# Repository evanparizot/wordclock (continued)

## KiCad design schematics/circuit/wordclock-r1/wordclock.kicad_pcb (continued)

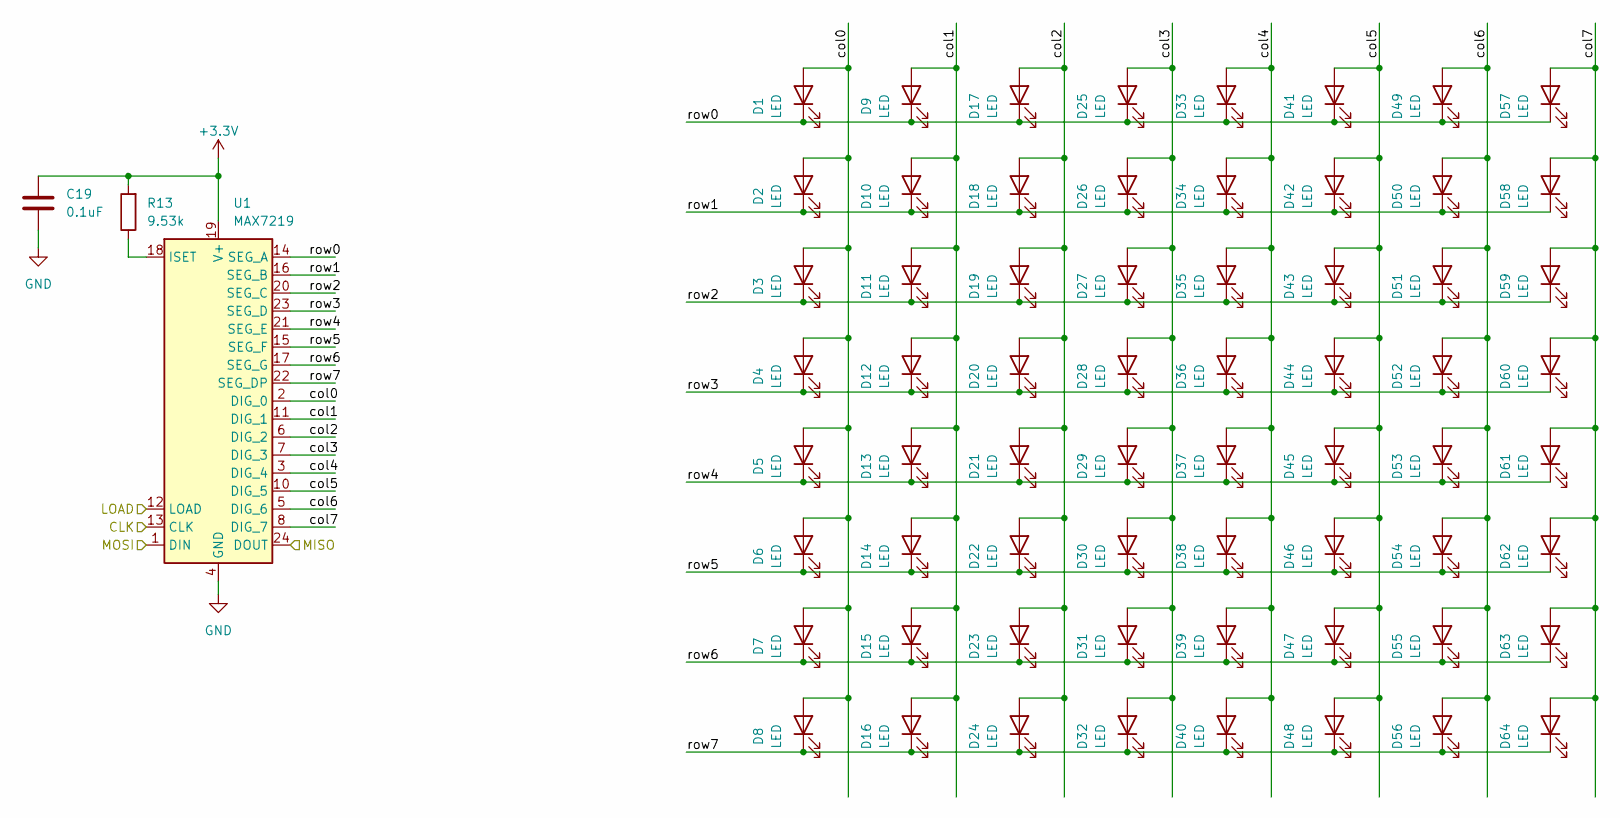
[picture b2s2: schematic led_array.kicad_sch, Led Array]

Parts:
C19: 0.1uF; C_0805_2012Metric
D1, D2, D3, D4, D5, D6, D7, D8, D9, D10, D11, D12, D13, D14, D15, D16, D17, D18, D19, D20, D21, D22, D23, D24, D25, D26, D27, D28, D29, D30, D31, D32, D33, D34, D35, D36, D37, D38, D39, D40, D41, D42, D43, D44, D45, D46, D47, D48, D49, D50, D51, D52, D53, D54, D55, D56, D57, D58, D59, D60, D61, D62, D63, D64: LED; LED_2010_5025Metric_Pad1.52x2.65mm_HandSolder
R13: 9.53k; R_0805_2012Metric
U1: MAX7219; SOIC-24W_7.5x15.4mm_P1.27mm

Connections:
+3.3V: C19.1, R13.2, U1.19 (V+); also elsewhere on the board
/Led Array 1/MISO: U1.24 (DOUT); also elsewhere on the board
/Led Array 1/col0: D1.2 (A), D2.2 (A), D3.2 (A), D4.2 (A), D5.2 (A), D6.2 (A), D7.2 (A), D8.2 (A), U1.2 (DIG_0)
/Led Array 1/col1: D9.2 (A), D10.2 (A), D11.2 (A), D12.2 (A), D13.2 (A), D14.2 (A), D15.2 (A), D16.2 (A), U1.11 (DIG_1)
/Led Array 1/col2: D17.2 (A), D18.2 (A), D19.2 (A), D20.2 (A), D21.2 (A), D22.2 (A), D23.2 (A), D24.2 (A), U1.6 (DIG_2)
/Led Array 1/col3: D25.2 (A), D26.2 (A), D27.2 (A), D28.2 (A), D29.2 (A), D30.2 (A), D31.2 (A), D32.2 (A), U1.7 (DIG_3)
/Led Array 1/col4: D33.2 (A), D34.2 (A), D35.2 (A), D36.2 (A), D37.2 (A), D38.2 (A), D39.2 (A), D40.2 (A), U1.3 (DIG_4)
/Led Array 1/col5: D41.2 (A), D42.2 (A), D43.2 (A), D44.2 (A), D45.2 (A), D46.2 (A), D47.2 (A), D48.2 (A), U1.10 (DIG_5)
/Led Array 1/col6: D49.2 (A), D50.2 (A), D51.2 (A), D52.2 (A), D53.2 (A), D54.2 (A), D55.2 (A), D56.2 (A), U1.5 (DIG_6)
/Led Array 1/col7: D57.2 (A), D58.2 (A), D59.2 (A), D60.2 (A), D61.2 (A), D62.2 (A), D63.2 (A), D64.2 (A), U1.8 (DIG_7)
/Led Array 1/row0: D1.1 (K), D9.1 (K), D17.1 (K), D25.1 (K), D33.1 (K), D41.1 (K), D49.1 (K), D57.1 (K), U1.14 (SEG_A)
/Led Array 1/row1: D2.1 (K), D10.1 (K), D18.1 (K), D26.1 (K), D34.1 (K), D42.1 (K), D50.1 (K), D58.1 (K), U1.16 (SEG_B)
/Led Array 1/row2: D3.1 (K), D11.1 (K), D19.1 (K), D27.1 (K), D35.1 (K), D43.1 (K), D51.1 (K), D59.1 (K), U1.20 (SEG_C)
/Led Array 1/row3: D4.1 (K), D12.1 (K), D20.1 (K), D28.1 (K), D36.1 (K), D44.1 (K), D52.1 (K), D60.1 (K), U1.23 (SEG_D)
/Led Array 1/row4: D5.1 (K), D13.1 (K), D21.1 (K), D29.1 (K), D37.1 (K), D45.1 (K), D53.1 (K), D61.1 (K), U1.21 (SEG_E)
/Led Array 1/row5: D6.1 (K), D14.1 (K), D22.1 (K), D30.1 (K), D38.1 (K), D46.1 (K), D54.1 (K), D62.1 (K), U1.15 (SEG_F)
/Led Array 1/row6: D7.1 (K), D15.1 (K), D23.1 (K), D31.1 (K), D39.1 (K), D47.1 (K), D55.1 (K), D63.1 (K), U1.17 (SEG_G)
/Led Array 1/row7: D8.1 (K), D16.1 (K), D24.1 (K), D32.1 (K), D40.1 (K), D48.1 (K), D56.1 (K), D64.1 (K), U1.22 (SEG_DP)
GND: C19.2, U1.4 (GND), U1.9 (GND); also elsewhere on the board
unnamed: R13.1, U1.18 (ISET)
SPI2_CLK: U1.13 (CLK); also elsewhere on the board
SPI2_LOAD: U1.12 (LOAD); also elsewhere on the board
SPI2_MOSI: U1.1 (DIN); also elsewhere on the board

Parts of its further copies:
C20, C21, C22: 0.1uF; C_0805_2012Metric
D65, D66, D67, D68, D69, D70, D71, D72, D73, D74, D75, D76, D77, D78, D79, D80, D81, D82, D83, D84, D85, D86, D87, D88, D89, D90, D91, D92, D93, D94, D95, D96, D97, D98, D99, D100, D101, D102, D103, D104, D105, D106, D107, D108, D109, D110, D111, D112, D113, D114, D115, D116, D117, D118, D119, D120, D121, D122, D123, D124, D125, D126, D127, D128, D129, D130, D131, D132, D133, D134, D135, D136, D137, D138, D139, D140, D141, D142, D143, D144, D145, D146, D147, D148, D149, D150, D151, D152, D153, D154, D155, D156, D157, D158, D159, D160, D161, D162, D163, D164, D165, D166, D167, D168, D169, D170, D171, D172, D173, D174, D175, D176, D177, D178, D179, D180, D181, D182, D183, D184, D185, D186, D187, D188, D189, D190, D191, D192, D193, D194, D195, D196, D197, D198, D199, D200, D201, D202, D203, D204, D205, D206, D207, D208, D209, D210, D211, D212, D213, D214, D215, D216, D217, D218, D219, D220, D221, D222, D223, D224, D225, D226, D227, D228, D229, D230, D231, D232, D233, D234, D235, D236, D237, D238, D239, D240, D241, D242, D243, D244, D245, D246, D247, D248, D249, D250, D251, D252, D253, D254, D255, D256: LED; LED_2010_5025Metric_Pad1.52x2.65mm_HandSolder
R14, R15, R16: 9.53k; R_0805_2012Metric
U2, U3, U4: MAX7219; SOIC-24W_7.5x15.4mm_P1.27mm

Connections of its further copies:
+3.3V: C20.1, C21.1, C22.1, R14.2, R15.2, R16.2, U2.19 (V+), U3.19 (V+), U4.19 (V+); also elsewhere on the board
/Led Array 1/MISO: U2.1 (DIN); also elsewhere on the board
/Led Array 2/MISO: U2.24 (DOUT), U3.1 (DIN)
/Led Array 2/col0: D65.2 (A), D66.2 (A), D67.2 (A), D68.2 (A), D69.2 (A), D70.2 (A), D71.2 (A), D72.2 (A), U2.2 (DIG_0)
/Led Array 2/col1: D73.2 (A), D74.2 (A), D75.2 (A), D76.2 (A), D77.2 (A), D78.2 (A), D79.2 (A), D80.2 (A), U2.11 (DIG_1)
/Led Array 2/col2: D81.2 (A), D82.2 (A), D83.2 (A), D84.2 (A), D85.2 (A), D86.2 (A), D87.2 (A), D88.2 (A), U2.6 (DIG_2)
/Led Array 2/col3: D89.2 (A), D90.2 (A), D91.2 (A), D92.2 (A), D93.2 (A), D94.2 (A), D95.2 (A), D96.2 (A), U2.7 (DIG_3)
/Led Array 2/col4: D97.2 (A), D98.2 (A), D99.2 (A), D100.2 (A), D101.2 (A), D102.2 (A), D103.2 (A), D104.2 (A), U2.3 (DIG_4)
/Led Array 2/col5: D105.2 (A), D106.2 (A), D107.2 (A), D108.2 (A), D109.2 (A), D110.2 (A), D111.2 (A), D112.2 (A), U2.10 (DIG_5)
/Led Array 2/col6: D113.2 (A), D114.2 (A), D115.2 (A), D116.2 (A), D117.2 (A), D118.2 (A), D119.2 (A), D120.2 (A), U2.5 (DIG_6)
/Led Array 2/col7: D121.2 (A), D122.2 (A), D123.2 (A), D124.2 (A), D125.2 (A), D126.2 (A), D127.2 (A), D128.2 (A), U2.8 (DIG_7)
/Led Array 2/row0: D65.1 (K), D73.1 (K), D81.1 (K), D89.1 (K), D97.1 (K), D105.1 (K), D113.1 (K), D121.1 (K), U2.14 (SEG_A)
/Led Array 2/row1: D66.1 (K), D74.1 (K), D82.1 (K), D90.1 (K), D98.1 (K), D106.1 (K), D114.1 (K), D122.1 (K), U2.16 (SEG_B)
/Led Array 2/row2: D67.1 (K), D75.1 (K), D83.1 (K), D91.1 (K), D99.1 (K), D107.1 (K), D115.1 (K), D123.1 (K), U2.20 (SEG_C)
/Led Array 2/row3: D68.1 (K), D76.1 (K), D84.1 (K), D92.1 (K), D100.1 (K), D108.1 (K), D116.1 (K), D124.1 (K), U2.23 (SEG_D)
/Led Array 2/row4: D69.1 (K), D77.1 (K), D85.1 (K), D93.1 (K), D101.1 (K), D109.1 (K), D117.1 (K), D125.1 (K), U2.21 (SEG_E)
/Led Array 2/row5: D70.1 (K), D78.1 (K), D86.1 (K), D94.1 (K), D102.1 (K), D110.1 (K), D118.1 (K), D126.1 (K), U2.15 (SEG_F)
/Led Array 2/row6: D71.1 (K), D79.1 (K), D87.1 (K), D95.1 (K), D103.1 (K), D111.1 (K), D119.1 (K), D127.1 (K), U2.17 (SEG_G)
/Led Array 2/row7: D72.1 (K), D80.1 (K), D88.1 (K), D96.1 (K), D104.1 (K), D112.1 (K), D120.1 (K), D128.1 (K), U2.22 (SEG_DP)
/Led Array 3/MISO: U3.24 (DOUT), U4.1 (DIN)
/Led Array 3/col0: D129.2 (A), D130.2 (A), D131.2 (A), D132.2 (A), D133.2 (A), D134.2 (A), D135.2 (A), D136.2 (A), U3.2 (DIG_0)
/Led Array 3/col1: D137.2 (A), D138.2 (A), D139.2 (A), D140.2 (A), D141.2 (A), D142.2 (A), D143.2 (A), D144.2 (A), U3.11 (DIG_1)
/Led Array 3/col2: D145.2 (A), D146.2 (A), D147.2 (A), D148.2 (A), D149.2 (A), D150.2 (A), D151.2 (A), D152.2 (A), U3.6 (DIG_2)
/Led Array 3/col3: D153.2 (A), D154.2 (A), D155.2 (A), D156.2 (A), D157.2 (A), D158.2 (A), D159.2 (A), D160.2 (A), U3.7 (DIG_3)
/Led Array 3/col4: D161.2 (A), D162.2 (A), D163.2 (A), D164.2 (A), D165.2 (A), D166.2 (A), D167.2 (A), D168.2 (A), U3.3 (DIG_4)
/Led Array 3/col5: D169.2 (A), D170.2 (A), D171.2 (A), D172.2 (A), D173.2 (A), D174.2 (A), D175.2 (A), D176.2 (A), U3.10 (DIG_5)
/Led Array 3/col6: D177.2 (A), D178.2 (A), D179.2 (A), D180.2 (A), D181.2 (A), D182.2 (A), D183.2 (A), D184.2 (A), U3.5 (DIG_6)
/Led Array 3/col7: D185.2 (A), D186.2 (A), D187.2 (A), D188.2 (A), D189.2 (A), D190.2 (A), D191.2 (A), D192.2 (A), U3.8 (DIG_7)
/Led Array 3/row0: D129.1 (K), D137.1 (K), D145.1 (K), D153.1 (K), D161.1 (K), D169.1 (K), D177.1 (K), D185.1 (K), U3.14 (SEG_A)
/Led Array 3/row1: D130.1 (K), D138.1 (K), D146.1 (K), D154.1 (K), D162.1 (K), D170.1 (K), D178.1 (K), D186.1 (K), U3.16 (SEG_B)
/Led Array 3/row2: D131.1 (K), D139.1 (K), D147.1 (K), D155.1 (K), D163.1 (K), D171.1 (K), D179.1 (K), D187.1 (K), U3.20 (SEG_C)
/Led Array 3/row3: D132.1 (K), D140.1 (K), D148.1 (K), D156.1 (K), D164.1 (K), D172.1 (K), D180.1 (K), D188.1 (K), U3.23 (SEG_D)
/Led Array 3/row4: D133.1 (K), D141.1 (K), D149.1 (K), D157.1 (K), D165.1 (K), D173.1 (K), D181.1 (K), D189.1 (K), U3.21 (SEG_E)
/Led Array 3/row5: D134.1 (K), D142.1 (K), D150.1 (K), D158.1 (K), D166.1 (K), D174.1 (K), D182.1 (K), D190.1 (K), U3.15 (SEG_F)
/Led Array 3/row6: D135.1 (K), D143.1 (K), D151.1 (K), D159.1 (K), D167.1 (K), D175.1 (K), D183.1 (K), D191.1 (K), U3.17 (SEG_G)
/Led Array 3/row7: D136.1 (K), D144.1 (K), D152.1 (K), D160.1 (K), D168.1 (K), D176.1 (K), D184.1 (K), D192.1 (K), U3.22 (SEG_DP)
/Led Array 4/col0: D193.2 (A), D194.2 (A), D195.2 (A), D196.2 (A), D197.2 (A), D198.2 (A), D199.2 (A), D200.2 (A), U4.2 (DIG_0)
/Led Array 4/col1: D201.2 (A), D202.2 (A), D203.2 (A), D204.2 (A), D205.2 (A), D206.2 (A), D207.2 (A), D208.2 (A), U4.11 (DIG_1)
/Led Array 4/col2: D209.2 (A), D210.2 (A), D211.2 (A), D212.2 (A), D213.2 (A), D214.2 (A), D215.2 (A), D216.2 (A), U4.6 (DIG_2)
/Led Array 4/col3: D217.2 (A), D218.2 (A), D219.2 (A), D220.2 (A), D221.2 (A), D222.2 (A), D223.2 (A), D224.2 (A), U4.7 (DIG_3)
/Led Array 4/col4: D225.2 (A), D226.2 (A), D227.2 (A), D228.2 (A), D229.2 (A), D230.2 (A), D231.2 (A), D232.2 (A), U4.3 (DIG_4)
/Led Array 4/col5: D233.2 (A), D234.2 (A), D235.2 (A), D236.2 (A), D237.2 (A), D238.2 (A), D239.2 (A), D240.2 (A), U4.10 (DIG_5)
/Led Array 4/col6: D241.2 (A), D242.2 (A), D243.2 (A), D244.2 (A), D245.2 (A), D246.2 (A), D247.2 (A), D248.2 (A), U4.5 (DIG_6)
/Led Array 4/col7: D249.2 (A), D250.2 (A), D251.2 (A), D252.2 (A), D253.2 (A), D254.2 (A), D255.2 (A), D256.2 (A), U4.8 (DIG_7)
/Led Array 4/row0: D193.1 (K), D201.1 (K), D209.1 (K), D217.1 (K), D225.1 (K), D233.1 (K), D241.1 (K), D249.1 (K), U4.14 (SEG_A)
/Led Array 4/row1: D194.1 (K), D202.1 (K), D210.1 (K), D218.1 (K), D226.1 (K), D234.1 (K), D242.1 (K), D250.1 (K), U4.16 (SEG_B)
/Led Array 4/row2: D195.1 (K), D203.1 (K), D211.1 (K), D219.1 (K), D227.1 (K), D235.1 (K), D243.1 (K), D251.1 (K), U4.20 (SEG_C)
/Led Array 4/row3: D196.1 (K), D204.1 (K), D212.1 (K), D220.1 (K), D228.1 (K), D236.1 (K), D244.1 (K), D252.1 (K), U4.23 (SEG_D)
/Led Array 4/row4: D197.1 (K), D205.1 (K), D213.1 (K), D221.1 (K), D229.1 (K), D237.1 (K), D245.1 (K), D253.1 (K), U4.21 (SEG_E)
/Led Array 4/row5: D198.1 (K), D206.1 (K), D214.1 (K), D222.1 (K), D230.1 (K), D238.1 (K), D246.1 (K), D254.1 (K), U4.15 (SEG_F)
/Led Array 4/row6: D199.1 (K), D207.1 (K), D215.1 (K), D223.1 (K), D231.1 (K), D239.1 (K), D247.1 (K), D255.1 (K), U4.17 (SEG_G)
/Led Array 4/row7: D200.1 (K), D208.1 (K), D216.1 (K), D224.1 (K), D232.1 (K), D240.1 (K), D248.1 (K), D256.1 (K), U4.22 (SEG_DP)
GND: C20.2, C21.2, C22.2, U2.4 (GND), U2.9 (GND), U3.4 (GND), U3.9 (GND), U4.4 (GND), U4.9 (GND); also elsewhere on the board
unnamed: R14.1, U2.18 (ISET)
unnamed: R15.1, U3.18 (ISET)
unnamed: R16.1, U4.18 (ISET)
SPI2_CLK: U2.13 (CLK), U3.13 (CLK), U4.13 (CLK); also elsewhere on the board
SPI2_LOAD: U2.12 (LOAD), U3.12 (LOAD), U4.12 (LOAD); also elsewhere on the board
SPI2_MISO: U4.24 (DOUT); also elsewhere on the board

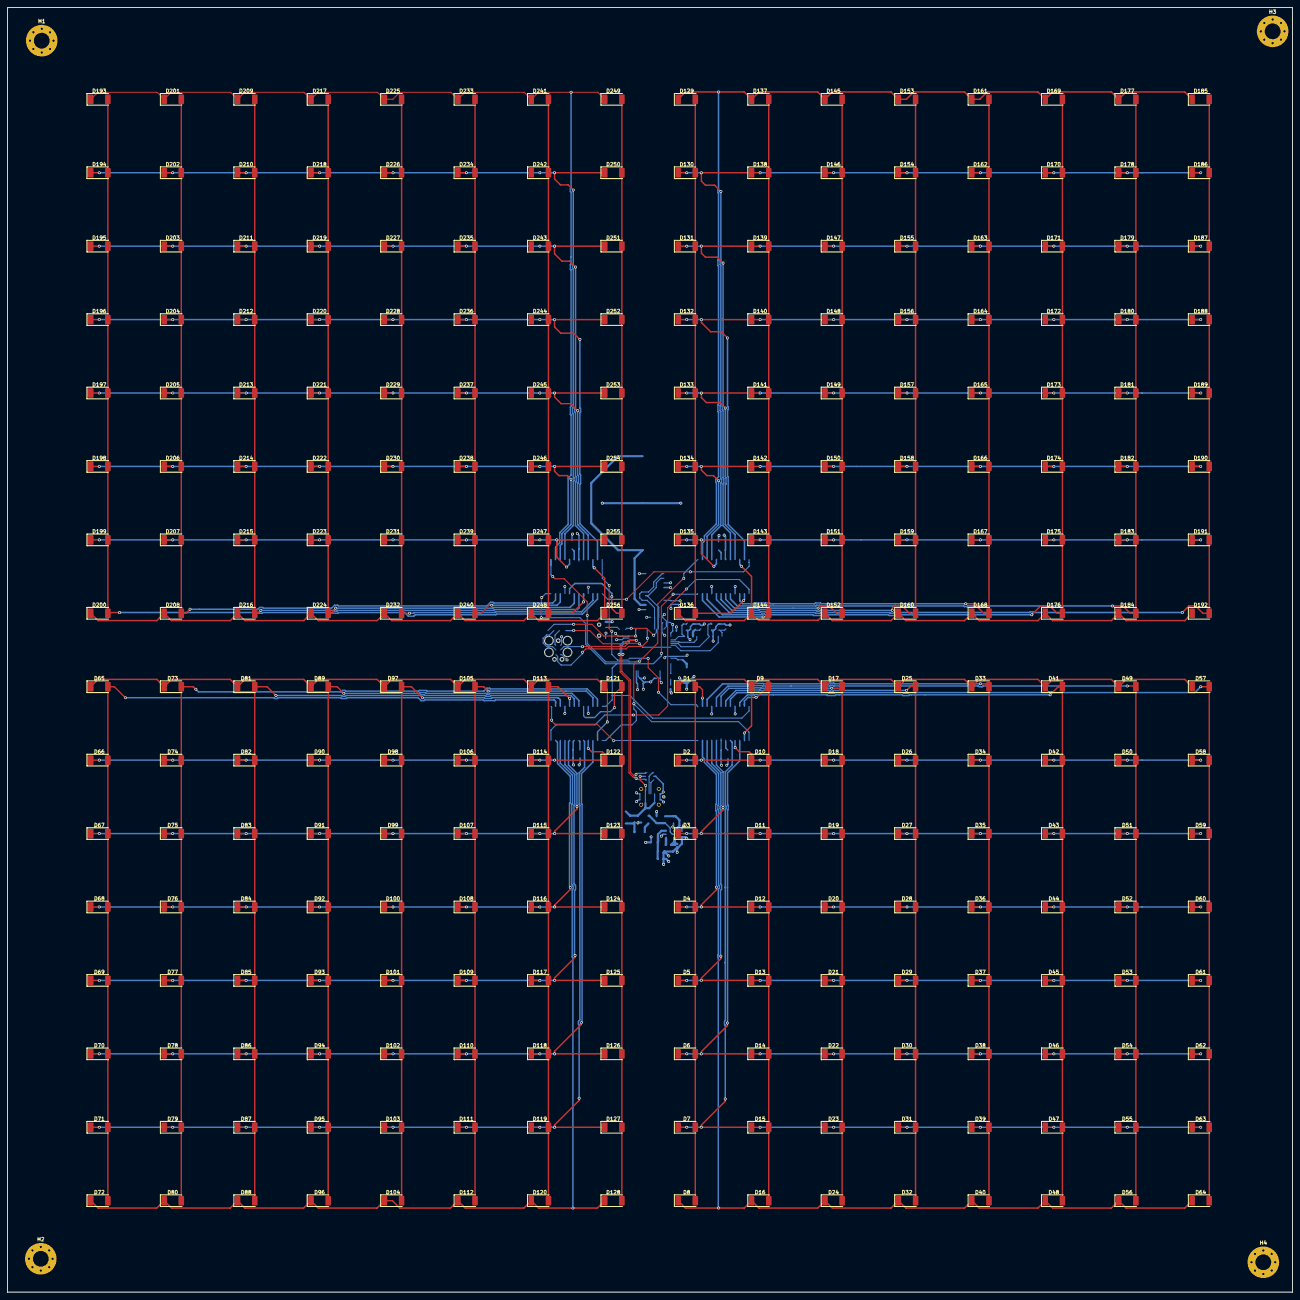
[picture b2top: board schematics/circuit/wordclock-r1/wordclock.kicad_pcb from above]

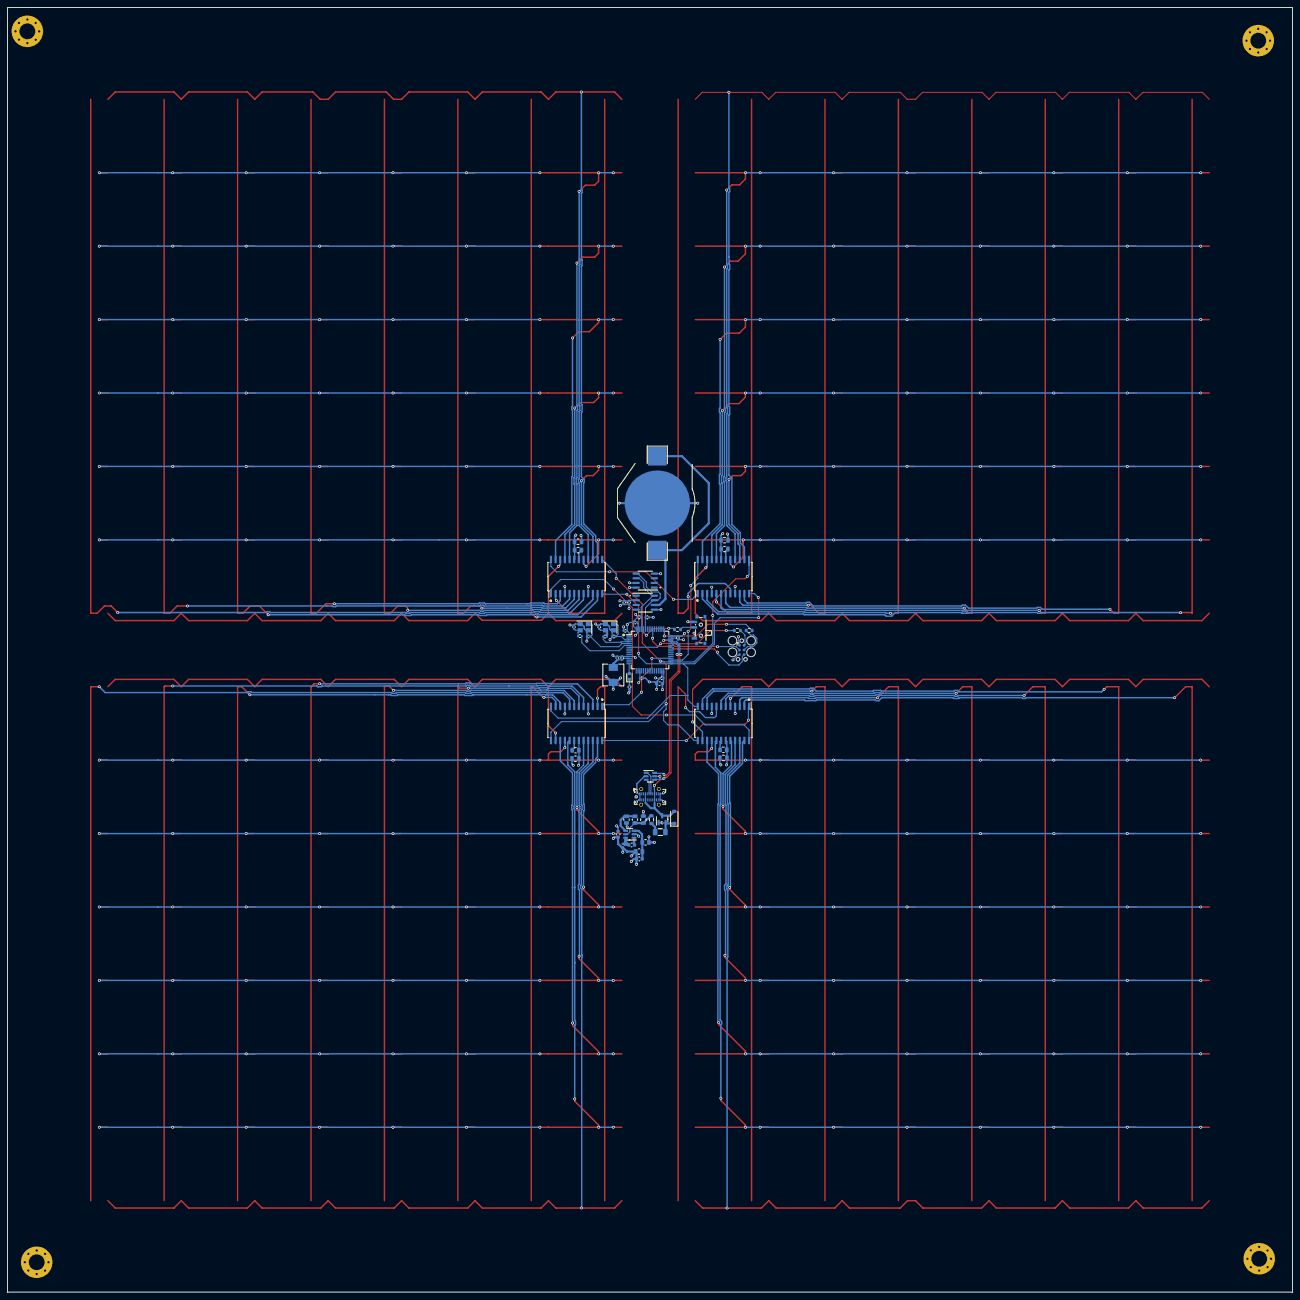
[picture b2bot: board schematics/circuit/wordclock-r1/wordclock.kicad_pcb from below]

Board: 4 copper layers, 350.0 x 349.9 mm, 320 parts (60 on the bottom side), 109 nets.

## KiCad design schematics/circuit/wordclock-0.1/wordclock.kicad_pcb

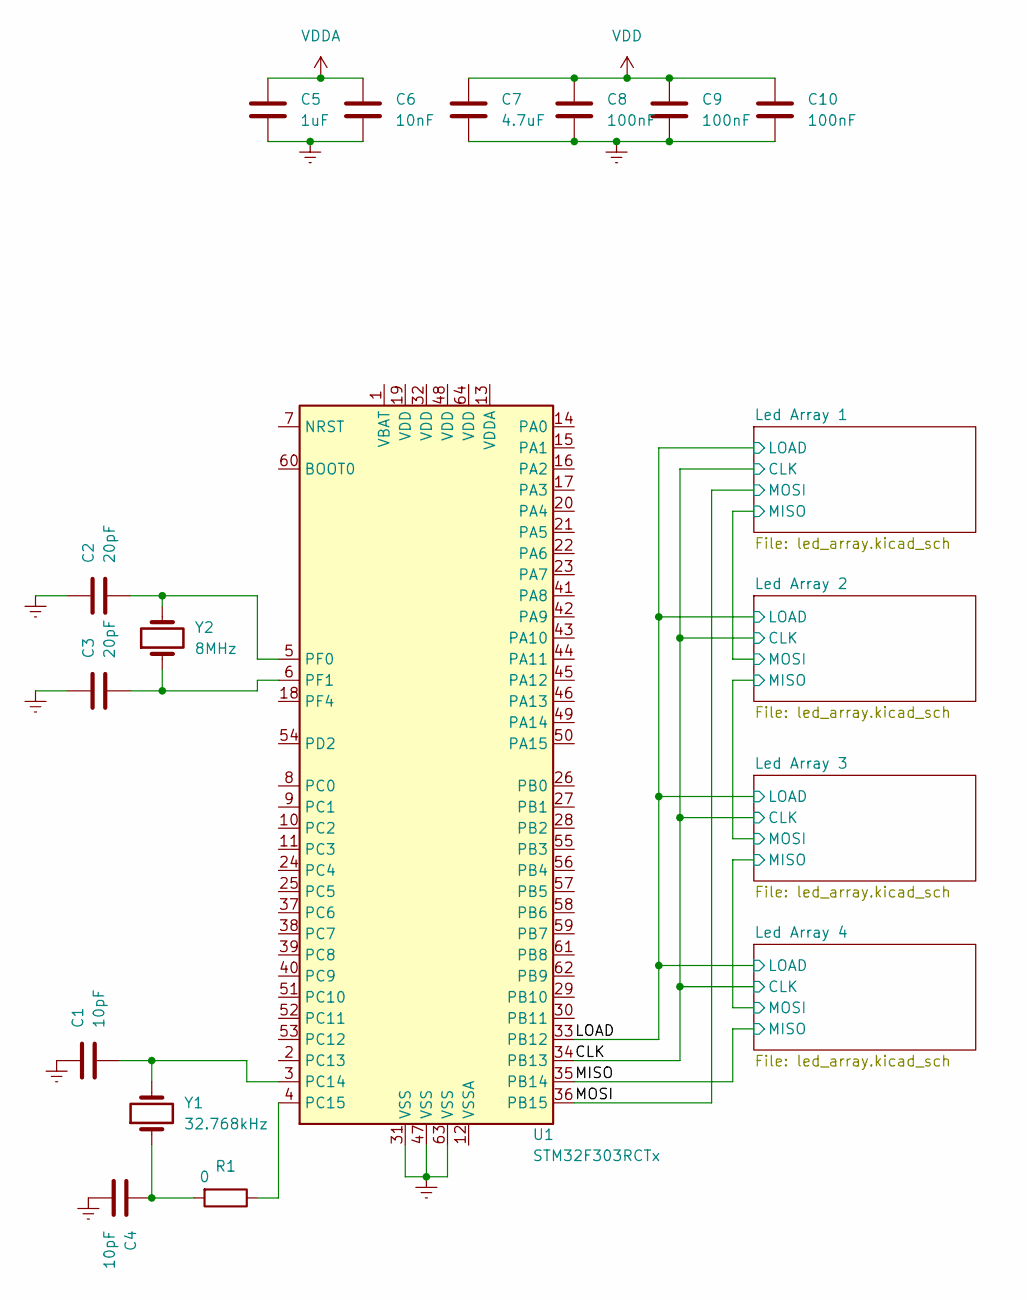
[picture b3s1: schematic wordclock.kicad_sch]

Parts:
C1, C4: 10pF; C_0805_2012Metric
C2, C3: 20pF; C_0805_2012Metric
C5: 1uF; C_0805_2012Metric
C6: 10nF; C_0805_2012Metric
C7: 4.7uF; C_0805_2012Metric
C8, C9, C10: 100nF; C_0805_2012Metric
R1: 0; R_1210_3225Metric
U1: STM32F303RCTx; LQFP-64_10x10mm_P0.5mm
Y1: 32.768kHz; Crystal_SMD_3225-4Pin_3.2x2.5mm
Y2: 8MHz; Crystal_SMD_3225-4Pin_3.2x2.5mm

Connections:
/CLK: U1.34 (PB13); also elsewhere on the board
/LOAD: U1.33 (PB12); also elsewhere on the board
/MISO: U1.35 (PB14); also elsewhere on the board
/MOSI: U1.36 (PB15); also elsewhere on the board
Earth: C1.1, C2.1, C3.1, C4.2, C5.2, C6.2, C7.2, C8.2, C9.2, C10.2, U1.31 (VSS), U1.47 (VSS), U1.63 (VSS)
unnamed: C4.1, R1.2, Y1.1
unnamed: C1.2, U1.3 (PC14), Y1.2
unnamed: R1.1, U1.4 (PC15)
unnamed: C2.2, U1.5 (PF0), Y2.2
unnamed: C3.2, U1.6 (PF1), Y2.1
VDD: C7.1, C8.1, C9.1, C10.1; also elsewhere on the board
VDDA: C5.1, C6.1

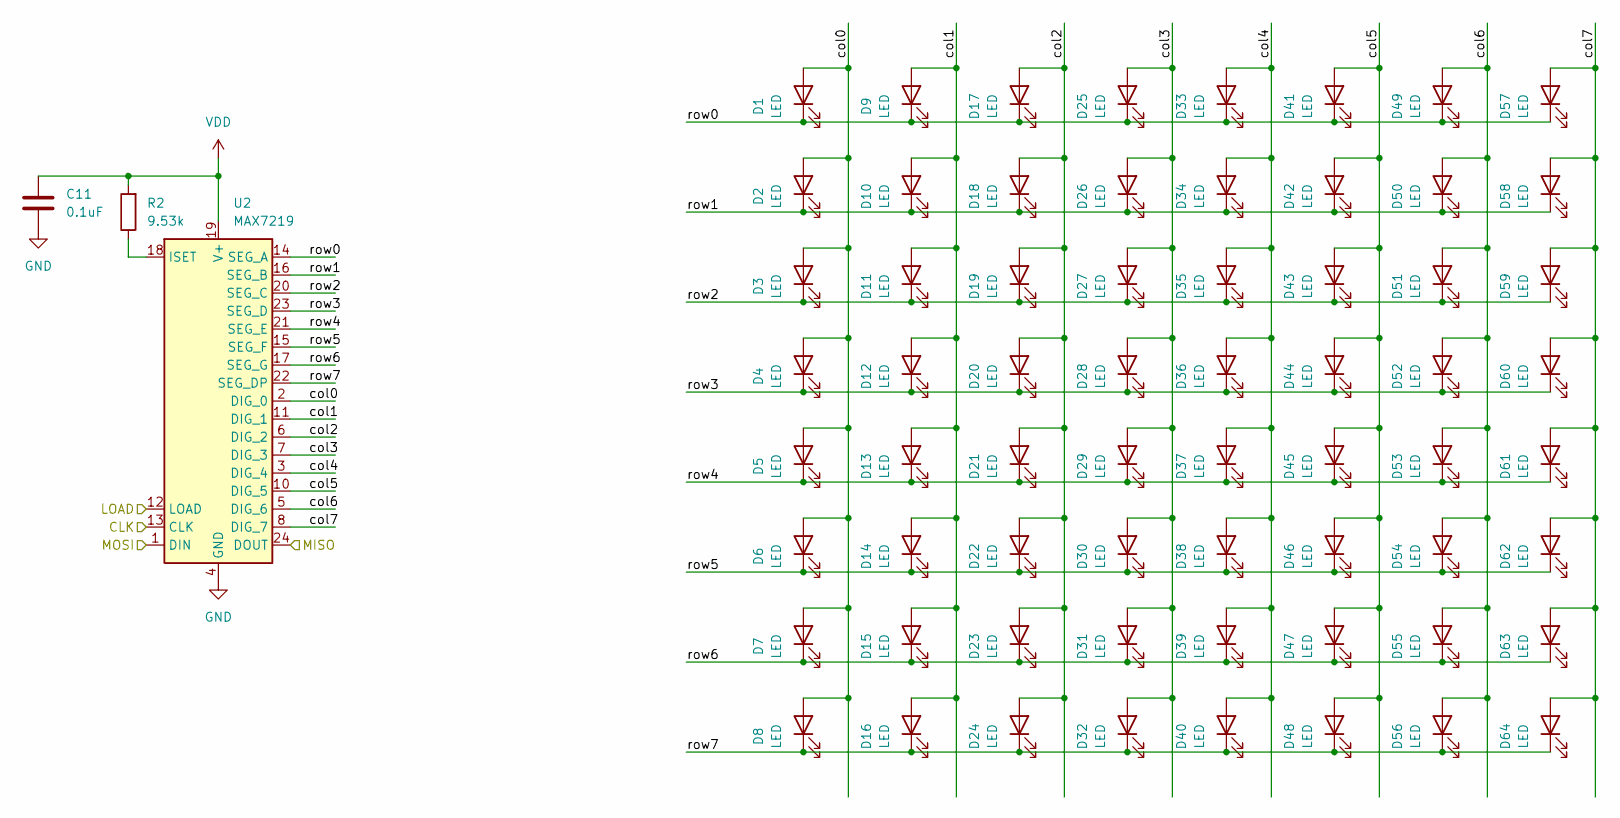
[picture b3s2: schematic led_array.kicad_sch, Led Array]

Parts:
C11: 0.1uF; C_0805_2012Metric
D1, D2, D3, D4, D5, D6, D7, D8, D9, D10, D11, D12, D13, D14, D15, D16, D17, D18, D19, D20, D21, D22, D23, D24, D25, D26, D27, D28, D29, D30, D31, D32, D33, D34, D35, D36, D37, D38, D39, D40, D41, D42, D43, D44, D45, D46, D47, D48, D49, D50, D51, D52, D53, D54, D55, D56, D57, D58, D59, D60, D61, D62, D63, D64: LED; LED_2010_5025Metric_Pad1.52x2.65mm_HandSolder
R2: 9.53k; R_0805_2012Metric
U2: MAX7219; SOIC-24W_7.5x15.4mm_P1.27mm

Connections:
/CLK: U2.13 (CLK); also elsewhere on the board
/LOAD: U2.12 (LOAD); also elsewhere on the board
/Led Array 1/MISO: U2.24 (DOUT); also elsewhere on the board
/Led Array 1/col0: D1.2 (A), D2.2 (A), D3.2 (A), D4.2 (A), D5.2 (A), D6.2 (A), D7.2 (A), D8.2 (A), U2.2 (DIG_0)
/Led Array 1/col1: D9.2 (A), D10.2 (A), D11.2 (A), D12.2 (A), D13.2 (A), D14.2 (A), D15.2 (A), D16.2 (A), U2.11 (DIG_1)
/Led Array 1/col2: D17.2 (A), D18.2 (A), D19.2 (A), D20.2 (A), D21.2 (A), D22.2 (A), D23.2 (A), D24.2 (A), U2.6 (DIG_2)
/Led Array 1/col3: D25.2 (A), D26.2 (A), D27.2 (A), D28.2 (A), D29.2 (A), D30.2 (A), D31.2 (A), D32.2 (A), U2.7 (DIG_3)
/Led Array 1/col4: D33.2 (A), D34.2 (A), D35.2 (A), D36.2 (A), D37.2 (A), D38.2 (A), D39.2 (A), D40.2 (A), U2.3 (DIG_4)
/Led Array 1/col5: D41.2 (A), D42.2 (A), D43.2 (A), D44.2 (A), D45.2 (A), D46.2 (A), D47.2 (A), D48.2 (A), U2.10 (DIG_5)
/Led Array 1/col6: D49.2 (A), D50.2 (A), D51.2 (A), D52.2 (A), D53.2 (A), D54.2 (A), D55.2 (A), D56.2 (A), U2.5 (DIG_6)
/Led Array 1/col7: D57.2 (A), D58.2 (A), D59.2 (A), D60.2 (A), D61.2 (A), D62.2 (A), D63.2 (A), D64.2 (A), U2.8 (DIG_7)
/Led Array 1/row0: D1.1 (K), D9.1 (K), D17.1 (K), D25.1 (K), D33.1 (K), D41.1 (K), D49.1 (K), D57.1 (K), U2.14 (SEG_A)
/Led Array 1/row1: D2.1 (K), D10.1 (K), D18.1 (K), D26.1 (K), D34.1 (K), D42.1 (K), D50.1 (K), D58.1 (K), U2.16 (SEG_B)
/Led Array 1/row2: D3.1 (K), D11.1 (K), D19.1 (K), D27.1 (K), D35.1 (K), D43.1 (K), D51.1 (K), D59.1 (K), U2.20 (SEG_C)
/Led Array 1/row3: D4.1 (K), D12.1 (K), D20.1 (K), D28.1 (K), D36.1 (K), D44.1 (K), D52.1 (K), D60.1 (K), U2.23 (SEG_D)
/Led Array 1/row4: D5.1 (K), D13.1 (K), D21.1 (K), D29.1 (K), D37.1 (K), D45.1 (K), D53.1 (K), D61.1 (K), U2.21 (SEG_E)
/Led Array 1/row5: D6.1 (K), D14.1 (K), D22.1 (K), D30.1 (K), D38.1 (K), D46.1 (K), D54.1 (K), D62.1 (K), U2.15 (SEG_F)
/Led Array 1/row6: D7.1 (K), D15.1 (K), D23.1 (K), D31.1 (K), D39.1 (K), D47.1 (K), D55.1 (K), D63.1 (K), U2.17 (SEG_G)
/Led Array 1/row7: D8.1 (K), D16.1 (K), D24.1 (K), D32.1 (K), D40.1 (K), D48.1 (K), D56.1 (K), D64.1 (K), U2.22 (SEG_DP)
/MOSI: U2.1 (DIN); also elsewhere on the board
GND: C11.2, U2.4 (GND), U2.9 (GND); also elsewhere on the board
unnamed: R2.1, U2.18 (ISET)
VDD: C11.1, R2.2, U2.19 (V+); also elsewhere on the board

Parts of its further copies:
C12, C13, C14: 0.1uF; C_0805_2012Metric
D65, D66, D67, D68, D69, D70, D71, D72, D73, D74, D75, D76, D77, D78, D79, D80, D81, D82, D83, D84, D85, D86, D87, D88, D89, D90, D91, D92, D93, D94, D95, D96, D97, D98, D99, D100, D101, D102, D103, D104, D105, D106, D107, D108, D109, D110, D111, D112, D113, D114, D115, D116, D117, D118, D119, D120, D121, D122, D123, D124, D125, D126, D127, D128, D129, D130, D131, D132, D133, D134, D135, D136, D137, D138, D139, D140, D141, D142, D143, D144, D145, D146, D147, D148, D149, D150, D151, D152, D153, D154, D155, D156, D157, D158, D159, D160, D161, D162, D163, D164, D165, D166, D167, D168, D169, D170, D171, D172, D173, D174, D175, D176, D177, D178, D179, D180, D181, D182, D183, D184, D185, D186, D187, D188, D189, D190, D191, D192, D193, D194, D195, D196, D197, D198, D199, D200, D201, D202, D203, D204, D205, D206, D207, D208, D209, D210, D211, D212, D213, D214, D215, D216, D217, D218, D219, D220, D221, D222, D223, D224, D225, D226, D227, D228, D229, D230, D231, D232, D233, D234, D235, D236, D237, D238, D239, D240, D241, D242, D243, D244, D245, D246, D247, D248, D249, D250, D251, D252, D253, D254, D255, D256: LED; LED_2010_5025Metric_Pad1.52x2.65mm_HandSolder
R3, R4, R5: 9.53k; R_0805_2012Metric
U3, U4, U5: MAX7219; SOIC-24W_7.5x15.4mm_P1.27mm

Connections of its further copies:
/CLK: U3.13 (CLK), U4.13 (CLK), U5.13 (CLK); also elsewhere on the board
/LOAD: U3.12 (LOAD), U4.12 (LOAD), U5.12 (LOAD); also elsewhere on the board
/Led Array 1/MISO: U3.1 (DIN); also elsewhere on the board
/Led Array 2/MISO: U3.24 (DOUT), U4.1 (DIN)
/Led Array 2/col0: D65.2 (A), D66.2 (A), D67.2 (A), D68.2 (A), D69.2 (A), D70.2 (A), D71.2 (A), D72.2 (A), U3.2 (DIG_0)
/Led Array 2/col1: D73.2 (A), D74.2 (A), D75.2 (A), D76.2 (A), D77.2 (A), D78.2 (A), D79.2 (A), D80.2 (A), U3.11 (DIG_1)
/Led Array 2/col2: D81.2 (A), D82.2 (A), D83.2 (A), D84.2 (A), D85.2 (A), D86.2 (A), D87.2 (A), D88.2 (A), U3.6 (DIG_2)
/Led Array 2/col3: D89.2 (A), D90.2 (A), D91.2 (A), D92.2 (A), D93.2 (A), D94.2 (A), D95.2 (A), D96.2 (A), U3.7 (DIG_3)
/Led Array 2/col4: D97.2 (A), D98.2 (A), D99.2 (A), D100.2 (A), D101.2 (A), D102.2 (A), D103.2 (A), D104.2 (A), U3.3 (DIG_4)
/Led Array 2/col5: D105.2 (A), D106.2 (A), D107.2 (A), D108.2 (A), D109.2 (A), D110.2 (A), D111.2 (A), D112.2 (A), U3.10 (DIG_5)
/Led Array 2/col6: D113.2 (A), D114.2 (A), D115.2 (A), D116.2 (A), D117.2 (A), D118.2 (A), D119.2 (A), D120.2 (A), U3.5 (DIG_6)
/Led Array 2/col7: D121.2 (A), D122.2 (A), D123.2 (A), D124.2 (A), D125.2 (A), D126.2 (A), D127.2 (A), D128.2 (A), U3.8 (DIG_7)
/Led Array 2/row0: D65.1 (K), D73.1 (K), D81.1 (K), D89.1 (K), D97.1 (K), D105.1 (K), D113.1 (K), D121.1 (K), U3.14 (SEG_A)
/Led Array 2/row1: D66.1 (K), D74.1 (K), D82.1 (K), D90.1 (K), D98.1 (K), D106.1 (K), D114.1 (K), D122.1 (K), U3.16 (SEG_B)
/Led Array 2/row2: D67.1 (K), D75.1 (K), D83.1 (K), D91.1 (K), D99.1 (K), D107.1 (K), D115.1 (K), D123.1 (K), U3.20 (SEG_C)
/Led Array 2/row3: D68.1 (K), D76.1 (K), D84.1 (K), D92.1 (K), D100.1 (K), D108.1 (K), D116.1 (K), D124.1 (K), U3.23 (SEG_D)
/Led Array 2/row4: D69.1 (K), D77.1 (K), D85.1 (K), D93.1 (K), D101.1 (K), D109.1 (K), D117.1 (K), D125.1 (K), U3.21 (SEG_E)
/Led Array 2/row5: D70.1 (K), D78.1 (K), D86.1 (K), D94.1 (K), D102.1 (K), D110.1 (K), D118.1 (K), D126.1 (K), U3.15 (SEG_F)
/Led Array 2/row6: D71.1 (K), D79.1 (K), D87.1 (K), D95.1 (K), D103.1 (K), D111.1 (K), D119.1 (K), D127.1 (K), U3.17 (SEG_G)
/Led Array 2/row7: D72.1 (K), D80.1 (K), D88.1 (K), D96.1 (K), D104.1 (K), D112.1 (K), D120.1 (K), D128.1 (K), U3.22 (SEG_DP)
/Led Array 3/MISO: U4.24 (DOUT), U5.1 (DIN)
/Led Array 3/col0: D129.2 (A), D130.2 (A), D131.2 (A), D132.2 (A), D133.2 (A), D134.2 (A), D135.2 (A), D136.2 (A), U4.2 (DIG_0)
/Led Array 3/col1: D137.2 (A), D138.2 (A), D139.2 (A), D140.2 (A), D141.2 (A), D142.2 (A), D143.2 (A), D144.2 (A), U4.11 (DIG_1)
/Led Array 3/col2: D145.2 (A), D146.2 (A), D147.2 (A), D148.2 (A), D149.2 (A), D150.2 (A), D151.2 (A), D152.2 (A), U4.6 (DIG_2)
/Led Array 3/col3: D153.2 (A), D154.2 (A), D155.2 (A), D156.2 (A), D157.2 (A), D158.2 (A), D159.2 (A), D160.2 (A), U4.7 (DIG_3)
/Led Array 3/col4: D161.2 (A), D162.2 (A), D163.2 (A), D164.2 (A), D165.2 (A), D166.2 (A), D167.2 (A), D168.2 (A), U4.3 (DIG_4)
/Led Array 3/col5: D169.2 (A), D170.2 (A), D171.2 (A), D172.2 (A), D173.2 (A), D174.2 (A), D175.2 (A), D176.2 (A), U4.10 (DIG_5)
/Led Array 3/col6: D177.2 (A), D178.2 (A), D179.2 (A), D180.2 (A), D181.2 (A), D182.2 (A), D183.2 (A), D184.2 (A), U4.5 (DIG_6)
/Led Array 3/col7: D185.2 (A), D186.2 (A), D187.2 (A), D188.2 (A), D189.2 (A), D190.2 (A), D191.2 (A), D192.2 (A), U4.8 (DIG_7)
/Led Array 3/row0: D129.1 (K), D137.1 (K), D145.1 (K), D153.1 (K), D161.1 (K), D169.1 (K), D177.1 (K), D185.1 (K), U4.14 (SEG_A)
/Led Array 3/row1: D130.1 (K), D138.1 (K), D146.1 (K), D154.1 (K), D162.1 (K), D170.1 (K), D178.1 (K), D186.1 (K), U4.16 (SEG_B)
/Led Array 3/row2: D131.1 (K), D139.1 (K), D147.1 (K), D155.1 (K), D163.1 (K), D171.1 (K), D179.1 (K), D187.1 (K), U4.20 (SEG_C)
/Led Array 3/row3: D132.1 (K), D140.1 (K), D148.1 (K), D156.1 (K), D164.1 (K), D172.1 (K), D180.1 (K), D188.1 (K), U4.23 (SEG_D)
/Led Array 3/row4: D133.1 (K), D141.1 (K), D149.1 (K), D157.1 (K), D165.1 (K), D173.1 (K), D181.1 (K), D189.1 (K), U4.21 (SEG_E)
/Led Array 3/row5: D134.1 (K), D142.1 (K), D150.1 (K), D158.1 (K), D166.1 (K), D174.1 (K), D182.1 (K), D190.1 (K), U4.15 (SEG_F)
/Led Array 3/row6: D135.1 (K), D143.1 (K), D151.1 (K), D159.1 (K), D167.1 (K), D175.1 (K), D183.1 (K), D191.1 (K), U4.17 (SEG_G)
/Led Array 3/row7: D136.1 (K), D144.1 (K), D152.1 (K), D160.1 (K), D168.1 (K), D176.1 (K), D184.1 (K), D192.1 (K), U4.22 (SEG_DP)
/Led Array 4/col0: D193.2 (A), D194.2 (A), D195.2 (A), D196.2 (A), D197.2 (A), D198.2 (A), D199.2 (A), D200.2 (A), U5.2 (DIG_0)
/Led Array 4/col1: D201.2 (A), D202.2 (A), D203.2 (A), D204.2 (A), D205.2 (A), D206.2 (A), D207.2 (A), D208.2 (A), U5.11 (DIG_1)
/Led Array 4/col2: D209.2 (A), D210.2 (A), D211.2 (A), D212.2 (A), D213.2 (A), D214.2 (A), D215.2 (A), D216.2 (A), U5.6 (DIG_2)
/Led Array 4/col3: D217.2 (A), D218.2 (A), D219.2 (A), D220.2 (A), D221.2 (A), D222.2 (A), D223.2 (A), D224.2 (A), U5.7 (DIG_3)
/Led Array 4/col4: D225.2 (A), D226.2 (A), D227.2 (A), D228.2 (A), D229.2 (A), D230.2 (A), D231.2 (A), D232.2 (A), U5.3 (DIG_4)
/Led Array 4/col5: D233.2 (A), D234.2 (A), D235.2 (A), D236.2 (A), D237.2 (A), D238.2 (A), D239.2 (A), D240.2 (A), U5.10 (DIG_5)
/Led Array 4/col6: D241.2 (A), D242.2 (A), D243.2 (A), D244.2 (A), D245.2 (A), D246.2 (A), D247.2 (A), D248.2 (A), U5.5 (DIG_6)
/Led Array 4/col7: D249.2 (A), D250.2 (A), D251.2 (A), D252.2 (A), D253.2 (A), D254.2 (A), D255.2 (A), D256.2 (A), U5.8 (DIG_7)
/Led Array 4/row0: D193.1 (K), D201.1 (K), D209.1 (K), D217.1 (K), D225.1 (K), D233.1 (K), D241.1 (K), D249.1 (K), U5.14 (SEG_A)
/Led Array 4/row1: D194.1 (K), D202.1 (K), D210.1 (K), D218.1 (K), D226.1 (K), D234.1 (K), D242.1 (K), D250.1 (K), U5.16 (SEG_B)
/Led Array 4/row2: D195.1 (K), D203.1 (K), D211.1 (K), D219.1 (K), D227.1 (K), D235.1 (K), D243.1 (K), D251.1 (K), U5.20 (SEG_C)
/Led Array 4/row3: D196.1 (K), D204.1 (K), D212.1 (K), D220.1 (K), D228.1 (K), D236.1 (K), D244.1 (K), D252.1 (K), U5.23 (SEG_D)
/Led Array 4/row4: D197.1 (K), D205.1 (K), D213.1 (K), D221.1 (K), D229.1 (K), D237.1 (K), D245.1 (K), D253.1 (K), U5.21 (SEG_E)
/Led Array 4/row5: D198.1 (K), D206.1 (K), D214.1 (K), D222.1 (K), D230.1 (K), D238.1 (K), D246.1 (K), D254.1 (K), U5.15 (SEG_F)
/Led Array 4/row6: D199.1 (K), D207.1 (K), D215.1 (K), D223.1 (K), D231.1 (K), D239.1 (K), D247.1 (K), D255.1 (K), U5.17 (SEG_G)
/Led Array 4/row7: D200.1 (K), D208.1 (K), D216.1 (K), D224.1 (K), D232.1 (K), D240.1 (K), D248.1 (K), D256.1 (K), U5.22 (SEG_DP)
/MISO: U5.24 (DOUT); also elsewhere on the board
GND: C12.2, C13.2, C14.2, U3.4 (GND), U3.9 (GND), U4.4 (GND), U4.9 (GND), U5.4 (GND), U5.9 (GND); also elsewhere on the board
unnamed: R3.1, U3.18 (ISET)
unnamed: R4.1, U4.18 (ISET)
unnamed: R5.1, U5.18 (ISET)
VDD: C12.1, C13.1, C14.1, R3.2, R4.2, R5.2, U3.19 (V+), U4.19 (V+), U5.19 (V+); also elsewhere on the board

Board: 2 copper layers, 282 parts (26 on the bottom side), 84 nets, no tracks yet.

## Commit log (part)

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2019-09-20 Create LICENSE
2020-03-14 Move files to repository
2020-03-17 Restructure project layout
2020-03-17 Update BOM
2021-05-06 Add initial rust source files
2021-05-14 Add initial stm32 source files
2021-05-14 Update readme with repo information
2021-05-14 Set theme jekyll-theme-midnight
2021-05-16 Update github pages and remove old files
2022-10-08 Initial commit of kicad schematics files
2022-10-10 Define basic led arrays and main processor circuit
2023-02-25 Remove unnecessary files
2023-02-25 Add stm32 power schematic datasheet
2023-02-27 Add initial GPIO initialization logic for SPI
2023-02-27 Add i2c initialization for ds3231 RTC
2023-04-03 Fix display initialization
2023-04-03 Add initial text layout files
2023-04-03 Add initial time matrices
2023-04-06 Add function to OR time matrices
2023-04-11 Add time setting method and match logic
2023-04-11 Add times initialization (#2)
    * Add initial time matrices
    * Add function to OR time matrices
    * Add time setting method and match logic
2023-04-12 Define initial times config
2023-04-13 Finish defining words, schematic updates
2023-04-13 Change mode selection passing
2023-04-14 change to rtic
2023-04-14 RTIC and Configs (#3)
    * Define initial times config
    * Finish defining words, schematic updates
    * Change mode selection passing
    * change to rtic
2023-04-15 Initial 16x16 wordclock layout
2023-04-15 Change tracked files
2023-05-03 Initial pcb layout
2023-05-05 Add prototype board project
2023-11-30 more pcb changes
2023-11-30 PCB 0.1 Changes (#4)
    * Initial 16x16 wordclock layout
    * Change tracked files
    * Initial pcb layout
    * Add prototype board project
    * more pcb changes
2023-11-30 Reorganize timing
2023-11-30 Define button interrupt
2023-12-02 More timing changes
2023-12-02 Initial implementation of time adjustment
2023-12-02 Implement hour and minute buttons
    Use EXTI0 and EXTI3 interrupts to Implement
    functionality to increment hours and minutes
2023-12-02 Implement button interrupts for hours, minutes (#5)
    * Reorganize timing
    * Define button interrupt
    * More timing changes
    * Initial implementation of time adjustment
    * Implement hour and minute buttons
    Use EXTI0 and EXTI3 interrupts to Implement
2025-07-12 Switch libraries for interrupt handling
2025-10-19 Implement improved display refresh functionality
2025-10-19 Implement heartbeat feature
2025-10-20 Implement auto-diming feature based on time
2025-10-20 Add a more dynamic mode selection upon compile time
2025-10-20 Implement minute leds and blink functionality
2025-10-20 Implement several features for rendering and button holds (#6)
    * Switch libraries for interrupt handling
    * Implement improved display refresh functionality
    * Implement heartbeat feature
    * Implement auto-diming feature based on time
    * Add a more dynamic mode selection upon compile time
    * Implement minute leds and blink functionality
